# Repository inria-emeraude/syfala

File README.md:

# syfala v0.10.0

Automatic compilation of Faust and C++ audio DSP programs for AMD/Xilinx FPGA platforms.

## Documentation and tutorials

The Syfala documentation is now centralized [here](https://inria-emeraude.github.io/syfala/). It includes information, examples and tutorials for the following topics: 

- Installing AMD/Xilinx **dependencies**.
- Installing and setting up the **syfala toolchain**.
- Running a simple example on a Digilent Zybo Z7 board, **using Faust**.
- Using C++ to program a more optimized DSP kernel.
- Building the **Embedded Linux** for Syfala.

## Supported board models

- [x] Digilent **Zybo Z7-10** - Zynq-7000 ARM/FPGA SoC Development Board
- [x] Digilent **Zybo Z7-20** - Zynq-7000 ARM/FPGA SoC Development Board
- [x] Digilent **Genesys ZU-3EG** - Zynq UltraScale+ MPSoC Development Board

and more to come...

## The syfala team

Here is a list of person that have contributed to the Syfala project :

- Tanguy Risset
- Yann Orlarey 
- Romain Michon
- Stephane Letz
- Florent de Dinechin
- Anastasia Volkova
- Alain Darte
- Yohan Uguen
- Gero Müller
- Adeyemi Gbadamosi
- Ousmane Touat
- Luc Forget
- Antonin Dudermel
- Maxime Popoff
- Thomas Delmas
- Oussama Bouksim
- Pierre Cochard
- Joseph Bizien
- Agathe Herrou
- Jurek Weber
- Aloïs Rautureau
- Jessica Zaki-Sewa
- Jonas Hoepner
- Benjamin Quiédeville
- Daniel Habib

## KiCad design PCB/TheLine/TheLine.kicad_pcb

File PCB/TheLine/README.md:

# The LINE

This directory contains the KiCad source files for **The LINE**, a modular 8-channel loudspeaker PCB module, along with `autogenerate.py`, a parametric generation script that can adapt the board layout to different loudspeaker dimensions and spacings without any manual PCB editing.

## Background

The LINE is an open-source, modular loudspeaker array platform designed for spatial audio research and artistic deployment. Each PCB module integrates eight MAX98357A digital audio amplifiers (DAC + Class-D power stage in one chip) and eight PCB-mounted loudspeakers. Modules are daisy-chained via identical 2×20 connectors and driven by an FPGA system-on-module (ALINX AC7020C, Xilinx Zynq-7000). A single FPGA can control up to three independent arrays of 32 modules each, for a theoretical maximum of 768 channels.

The PCB design is intentionally built around a repeated, identical functional block (one per loudspeaker) which makes the layout amenable to parametric generation. By specifying the loudspeaker width, height, and inter-speaker gap, `autogenerate.py` regenerates the full board layout automatically, repositioning all components, routing, zones, and silkscreen elements accordingly.

This approach was used, for instance, to adapt the board to the Tang Band W2-2136S loudspeakers used at the EMPAC/CCRMA installation at Stanford University, without modifying any schematic or routing logic by hand.

The full system is described in:

> Maxime Popoff, Romain Michon, Pierre Cochard, and Tanguy Risset.  
> *Embedded, Modular, and Affordable High-Density Loudspeaker Arrays.*  
> NIME '26, London, UK.

---

## Repository Structure

```
.
├── TheLine.kicad_pcb         # Template PCB (8-channel, default loudspeaker)
├── TheLine.kicad_sch         # KiCad schematic
├── TheLine.kicad_pro         # KiCad project file
├── autogenerate.py           # Parametric PCB generation script
├── gerbers/                  # Pre-generated Gerber files for the default design
└── README.md
```

The `autogenerate.py` script reads `TheLine.kicad_pcb` as its template and writes a new `.kicad_pcb` file with the updated geometry. It does not modify the schematic or the netlist.

---

## Dependencies

The script uses the **KiCad Python scripting API** (`pcbnew`), which is bundled with KiCad 7 and later. It does not require any additional Python packages.

**Requirements:**
- KiCad 7.x or 8.x installed
- Python 3.8+ (the one bundled with KiCad, or a system install where `pcbnew` is importable)

**Tested on Linux only**

---

## Usage

### Basic usage: change loudspeaker dimensions

```bash
python autogenerate.py \
  --input TheLine.kicad_pcb \
  --output TheLine_custom.kicad_pcb \
  --speaker-width 30.0 \
  --speaker-spacing 2.5 \
  --speaker-height 95.0
```

This generates a new board where each loudspeaker slot is 30 mm wide, separated by 2.5 mm gaps, with a board height of 95 mm. All component placements, tracks, copper zones, and silkscreen elements are repositioned accordingly.

### Preview without writing (dry run)

```bash
python autogenerate.py \
  --input TheLine.kicad_pcb \
  --output TheLine_custom.kicad_pcb \
  --speaker-width 30.0 \
  --dry-run
```

The script prints a summary of the computed geometry without writing any file. Useful for checking dimensions before committing.

### Replace the loudspeaker footprint

If your loudspeakers have a different pad layout than the default ASB05708CO-LW100-R, you can supply a custom footprint from a separate `.kicad_pcb` file. The script will extract the first `LS*`-referenced footprint from that file and substitute it for every speaker position on the generated board.

```bash
python autogenerate.py \
  --input TheLine.kicad_pcb \
  --output TheLine_custom.kicad_pcb \
  --speaker-width 38.0 \
  --speaker-spacing 3.0 \
  --custom-footprint my_speaker_footprint.kicad_pcb
```

The custom footprint board should contain exactly one footprint with a reference matching `LS\d+` (e.g. `LS1`). Pad net assignments are inferred automatically by pad number from the original design.

---

## Command-line Reference

| Argument | Type | Default | Description |
|---|---|---|---|
| `--input` | path | `../TheLine.kicad_pcb` | Input template PCB file |
| `--output` | path | `TheLine_parametric.kicad_pcb` | Output PCB file |
| `--speaker-width` | float (mm) | `23.0` | Width of one loudspeaker/amplifier block |
| `--speaker-spacing` | float (mm) | `2.0` | Gap between two adjacent blocks |
| `--speaker-height` | float (mm) | `90.0` | Board height (minimum 90 mm) |
| `--custom-footprint` | path | *(none)* | Path to a `.kicad_pcb` file whose first `LS*` footprint replaces every speaker footprint |
| `--dry-run` | flag | `False` | Print geometry summary without writing output |

---

## How the Script Works

The script operates entirely through the `pcbnew` API and does not touch the KiCad file as raw text (except for the footprint substitution step, which uses S-expression parsing for UUID deduplication).

At a high level, it:

1. Loads the template board and locates all `LS*` speaker footprints.
2. Computes the desired X positions of each speaker based on the requested width and spacing, starting from the leftmost speaker's current position.
3. For each component, track, copper zone, and silkscreen element in the parametric channel band, it determines which loudspeaker "column" it belongs to and applies the corresponding X offset.
4. Long horizontal bus tracks (the shared I²S/TDM signal bus) are stretched or compressed at both ends independently to span the full new board width.
5. The fixed solder-jumper strip (JP1–JP32, used for module addressing) is moved as a rigid group to stay flush with the right edge.
6. Connectors J1/J2 (left side) and J3/J4 (right side) are repositioned to maintain their distance from the board edges.
7. Power plane zones are redrawn to fill the new board outline.
8. Copper zones are refilled.
9. Speaker outlines are redrawn on `Dwgs.User` and `F.Silkscreen`.

The script preserves clock buffering connections and all net assignments. It does not regenerate routing for the signal fanout; those sections are moved rigidly.

---

## PCB Manufacturing Notes

The design targets standard 2-layer PCB manufacturing (1.6 mm FR4). The default board is approximately 190 × 90 mm. Most prototype PCB services (JLCPCB, PCBWay, etc.) can manufacture this size at low cost.

The maximum board size supported by this parametric approach, given typical manufacturer panel limits, is around 600 × 700 mm (which would accommodate a minimum loudspeaker spacing of approximately 75 mm in the most constrained configuration).

Pre-generated Gerber files for the default 8-speaker, 24 mm pitch configuration are in the `gerbers/` directory.

---

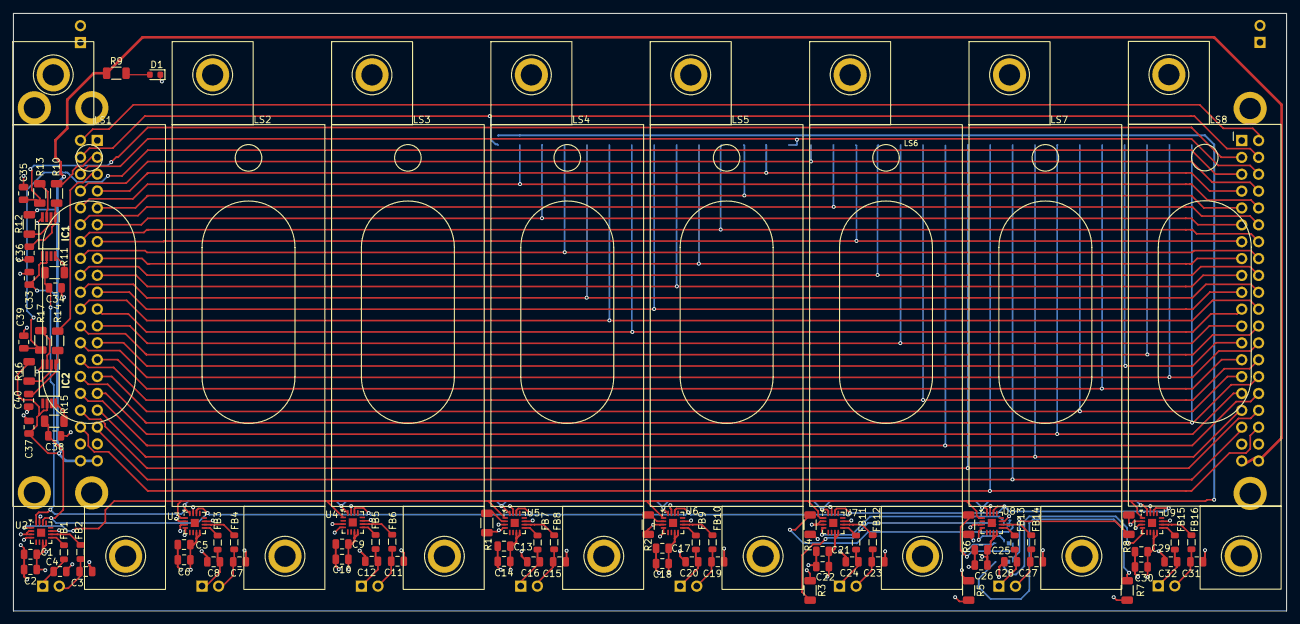
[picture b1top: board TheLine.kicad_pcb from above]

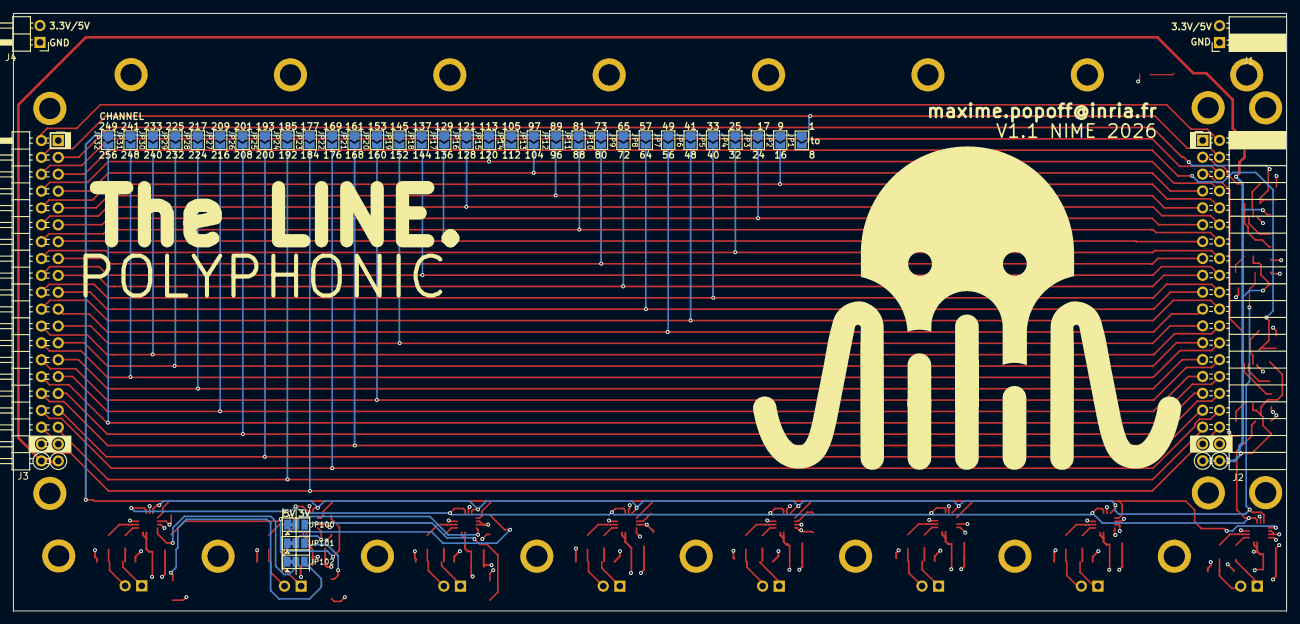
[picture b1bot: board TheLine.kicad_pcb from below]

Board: 4 copper layers, 191.8 x 90.0 mm, 131 parts (37 on the bottom side), 95 nets.

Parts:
C1, C5, C9, C13, C17, C21, C25, C29: 0.1uF; C_0805_2012Metric
C2, C6, C10, C14, C18, C22, C26, C30: 10uF; C_0805_2012Metric
C3, C4, C7, C8, C11, C12, C15, C16, C19, C20, C23, C24, C27, C28, C31, C32: 220p; C_0805_2012Metric
C33, C37: 100n; C_0805_2012Metric
C34, C35, C36, C38, C39, C40: DNP; C_0805_2012Metric
D1: LED; LED_0603_1608Metric
FB1, FB2, FB3, FB4, FB5, FB6, FB7, FB8, FB9, FB10, FB11, FB12, FB13, FB14, FB15, FB16: Ferrite; L_0805_2012Metric
IC1, IC2: LMK1C1102PWR; SOP65P640X120-8N
J1: Conn_01x02; PinSocket_1x02_P2.54mm_Horizontal
J2: Conn_02x20_Odd_Even; PinSocket_2x20_P2.54mm_Horizontal
J3: Conn_02x20_Odd_Even; PinHeader_2x20_P2.54mm_Horizontal
J4: Conn_01x02; PinHeader_1x02_P2.54mm_Horizontal
JP1, JP2, JP3, JP4, JP5, JP6, JP7, JP8, JP9, JP10, JP11, JP12, JP13, JP14, JP15, JP16, JP17, JP18, JP19, JP20, JP21, JP22, JP23, JP24, JP25, JP26, JP27, JP28, JP29, JP30, JP31, JP32: Jumper_2_Open; SolderJumper-2_P1.3mm_Open_TrianglePad1.0x1.5mm
JP100, JP101, JP102: jumper; SolderJumper-3_P1.3mm_Bridged12_Pad1.0x1.5mm
LS1, LS2, LS3, LS4, LS5, LS6, LS7, LS8: Speaker; ASB05708CO-LW100-R
R1, R2: 100k; R_1206_3216Metric
R3, R5, R7: 634k; R_1206_3216Metric
R4, R6, R8: 1M; R_1206_3216Metric
R9: 1k; R_1206_3216Metric
R10, R14: 22; R_1206_3216Metric
R11, R13, R15, R17: 0; R_1206_3216Metric
R12, R16: 10k; R_1206_3216Metric
U2, U3, U4, U5, U6, U7, U8, U9: MAX98357A; TQFN-16-1EP_3x3mm_P0.5mm_EP1.23x1.23mm

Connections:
/DAC1/OUT+: C4.1, FB1.2, LS1.1
/DAC1/OUT-: C3.1, FB2.2, LS1.2
/DAC2/OUT+: C8.1, FB3.2, LS2.1
/DAC2/OUT-: C7.1, FB4.2, LS2.2
/DAC3/OUT+: C12.1, FB5.2, LS3.1
/DAC3/OUT-: C11.1, FB6.2, LS3.2
/DAC4/GAIN: R1.1, U5.2 (GAIN_SLOT)
/DAC4/OUT+: C16.1, FB7.2, LS4.1
/DAC4/OUT-: C15.1, FB8.2, LS4.2
/DAC5/GAIN: R2.1, U6.2 (GAIN_SLOT)
/DAC5/OUT+: C20.1, FB9.2, LS5.1
/DAC5/OUT-: C19.1, FB10.2, LS5.2
/DAC6/MODE: JP100.2 (C), U7.4 (~SD_MODE)
/DAC6/OUT+: C24.1, FB11.2, LS6.1
/DAC6/OUT-: C23.1, FB12.2, LS6.2
/DAC7/MODE: JP101.2 (C), U8.4 (~SD_MODE)
/DAC7/OUT+: C28.1, FB13.2, LS7.1
/DAC7/OUT-: C27.1, FB14.2, LS7.2
/DAC8/MODE: JP102.2 (C), U9.4 (~SD_MODE)
/DAC8/OUT+: C32.1, FB15.2, LS8.1
/DAC8/OUT-: C31.1, FB16.2, LS8.2
/Pin_2: J2.2, J3.2
/Pin_3: J2.3, R10.1
/Pin_3_OUT: C35.2, J3.3, R13.1
/Pin_4: J2.4, J3.4, JP1.2 (B)
/Pin_5: J2.5, R14.1
/Pin_5_OUT: C39.2, J3.5, R17.1
/Pin_6: J2.6, J3.6, JP14.2 (B)
/Pin_7: J2.7, J3.7, JP13.2 (B)
/Pin_8: J2.8, J3.8, JP15.2 (B)
/Pin_9: J2.9, J3.9, JP12.2 (B)
/Pin_10: J2.10, J3.10, JP2.2 (B)
/Pin_11: J2.11, J3.11, JP3.2 (B)
/Pin_12: J2.12, J3.12, JP16.2 (B)
/Pin_13: J2.13, J3.13, JP17.2 (B)
/Pin_14: J2.14, J3.14, JP11.2 (B)
/Pin_15: J2.15, J3.15, JP10.2 (B)
/Pin_16: J2.16, J3.16, JP4.2 (B)
/Pin_17: J2.17, J3.17, JP9.2 (B)
/Pin_18: J2.18, J3.18, JP18.2 (B)
/Pin_19: J2.19, J3.19, JP8.2 (B)
/Pin_20: J2.20, J3.20, JP5.2 (B)
/Pin_21: J2.21, J3.21, JP7.2 (B)
/Pin_22: J2.22, J3.22, JP6.2 (B)
/Pin_23: J2.23, J3.23, JP19.2 (B)
/Pin_24: J2.24, J3.24, JP30.2 (B)
/Pin_25: J2.25, J3.25, JP29.2 (B)
/Pin_26: J2.26, J3.26, JP31.2 (B)
/Pin_27: J2.27, J3.27, JP28.2 (B)
/Pin_28: J2.28, J3.28, JP20.2 (B)
/Pin_29: J2.29, J3.29, JP27.2 (B)
/Pin_30: J2.30, J3.30, JP32.2 (B)
/Pin_31: J2.31, J3.31, JP26.2 (B)
/Pin_32: J2.32, J3.32, JP21.2 (B)
/Pin_33: J2.33, J3.33, JP25.2 (B)
/Pin_34: J2.34, J3.34, JP22.2 (B)
/Pin_35: J2.35, J3.35, JP24.2 (B)
/Pin_36: J2.36, J3.36, JP23.2 (B)
BCLK: C34.2, R11.2, U2.16 (BCLK), U3.16 (BCLK), U4.16 (BCLK), U5.16 (BCLK), U6.16 (BCLK), U7.16 (BCLK), U8.16 (BCLK), U9.16 (BCLK)
DIN: JP1.1 (A), JP2.1 (A), JP3.1 (A), JP4.1 (A), JP5.1 (A), JP6.1 (A), JP7.1 (A), JP8.1 (A), JP9.1 (A), JP10.1 (A), JP11.1 (A), JP12.1 (A), JP13.1 (A), JP14.1 (A), JP15.1 (A), JP16.1 (A), JP17.1 (A), JP18.1 (A), JP19.1 (A), JP20.1 (A), JP21.1 (A), JP22.1 (A), JP23.1 (A), JP24.1 (A), JP25.1 (A), JP26.1 (A), JP27.1 (A), JP28.1 (A), JP29.1 (A), JP30.1 (A), JP31.1 (A), JP32.1 (A), U2.1 (DIN), U3.1 (DIN), U4.1 (DIN), U5.1 (DIN), U6.1 (DIN), U7.1 (DIN), U8.1 (DIN), U9.1 (DIN)
GND: C1.2, C2.2, C3.2, C4.2, C5.2, C6.2, C7.2, C8.2, C9.2, C10.2, C11.2, C12.2, C13.2, C14.2, C15.2, C16.2, C17.2, C18.2, C19.2, C20.2, C21.2, C22.2, C23.2, C24.2, C25.2, C26.2, C27.2, C28.2, C29.2, C30.2, C31.2, C32.2, C33.2, C34.1, C35.1, C36.1, C37.2, C38.1, C39.1, C40.1, D1.1 (K), IC1.4 (GND), IC2.4 (GND), J1.1, J2.1, J2.37, J2.38, J3.1, J3.37, J3.38, J4.1, R2.2, U2.2 (GAIN_SLOT), U2.3 (GND), U2.11 (GND), U2.15 (GND), U3.3 (GND), U3.11 (GND), U3.15 (GND), U4.3 (GND), U4.11 (GND), U4.15 (GND), U5.3 (GND), U5.11 (GND), U5.15 (GND), U6.3 (GND), U6.11 (GND), U6.15 (GND), U7.2 (GAIN_SLOT), U7.3 (GND), U7.11 (GND), U7.15 (GND), U8.3 (GND), U8.11 (GND), U8.15 (GND), U9.3 (GND), U9.11 (GND), U9.15 (GND)
LRBCLK: C38.2, R15.2, U2.14 (LRCLK), U3.14 (LRCLK), U4.14 (LRCLK), U5.14 (LRCLK), U6.14 (LRCLK), U7.14 (LRCLK), U8.14 (LRCLK), U9.14 (LRCLK)
unnamed: D1.2 (A), R9.2
unnamed: IC1.2 (1G), R12.2
unnamed: C36.2, IC1.1 (CLKIN), R10.2
unnamed: IC1.3 (Y0), R13.2
unnamed: IC1.8 (Y1), R11.1
unnamed: IC2.2 (1G), R16.2
unnamed: C40.2, IC2.1 (CLKIN), R14.2
unnamed: IC2.3 (Y0), R17.2
unnamed: IC2.8 (Y1), R15.1
unnamed: JP100.1 (A), R4.1
unnamed: JP100.3 (B), R3.1
unnamed: JP101.1 (A), R6.1
unnamed: JP101.3 (B), R5.1
unnamed: JP102.1 (A), R8.1
unnamed: JP102.3 (B), R7.1
unnamed: FB2.1, U2.10 (OUTN)
unnamed: FB1.1, U2.9 (OUTP)
unnamed: FB4.1, U3.10 (OUTN)
unnamed: FB3.1, U3.9 (OUTP)
unnamed: FB6.1, U4.10 (OUTN)
unnamed: FB5.1, U4.9 (OUTP)
unnamed: FB8.1, U5.10 (OUTN)
unnamed: FB7.1, U5.9 (OUTP)
unnamed: FB10.1, U6.10 (OUTN)
unnamed: FB9.1, U6.9 (OUTP)
unnamed: FB12.1, U7.10 (OUTN)
unnamed: FB11.1, U7.9 (OUTP)
unnamed: FB14.1, U8.10 (OUTN)
unnamed: FB13.1, U8.9 (OUTP)
unnamed: FB16.1, U9.10 (OUTN)
unnamed: FB15.1, U9.9 (OUTP)
VCC: C33.1, C37.1, IC1.6 (VDD), IC2.6 (VDD), J2.39, J2.40, J3.39, J3.40, R9.1, R12.1, R16.1
VDD: C1.1, C2.1, C5.1, C6.1, C9.1, C10.1, C13.1, C14.1, C17.1, C18.1, C21.1, C22.1, C25.1, C26.1, C29.1, C30.1, J1.2, J4.2, R1.2, R3.2, R4.2, R5.2, R6.2, R7.2, R8.2, U2.4 (~SD_MODE), U2.7 (VDD), U2.8 (VDD), U3.2 (GAIN_SLOT), U3.4 (~SD_MODE), U3.7 (VDD), U3.8 (VDD), U4.4 (~SD_MODE), U4.7 (VDD), U4.8 (VDD), U5.4 (~SD_MODE), U5.7 (VDD), U5.8 (VDD), U6.4 (~SD_MODE), U6.7 (VDD), U6.8 (VDD), U7.7 (VDD), U7.8 (VDD), U8.7 (VDD), U8.8 (VDD), U9.2 (GAIN_SLOT), U9.7 (VDD), U9.8 (VDD)

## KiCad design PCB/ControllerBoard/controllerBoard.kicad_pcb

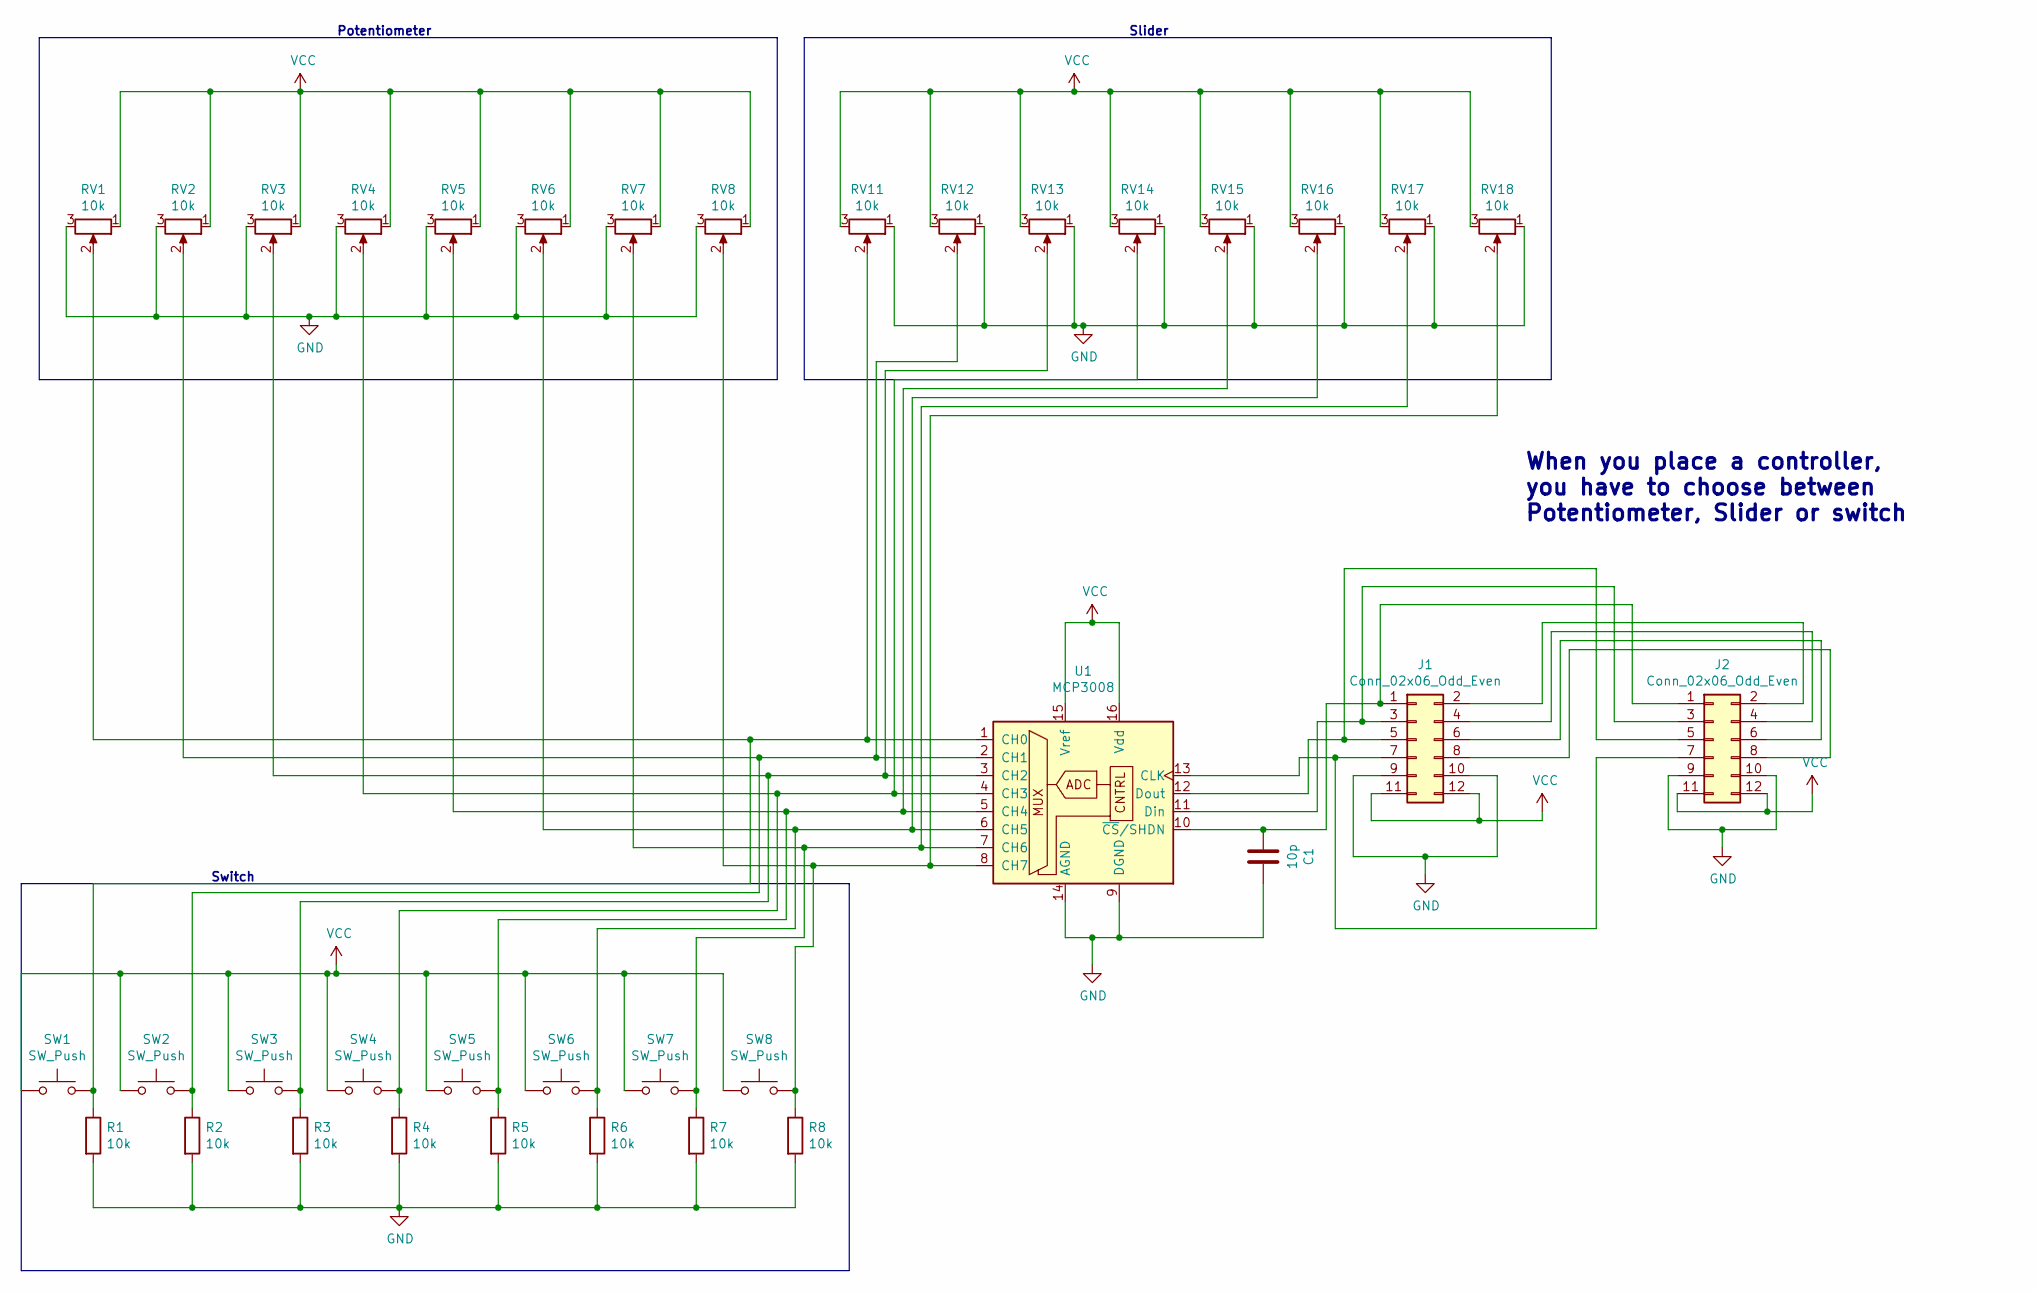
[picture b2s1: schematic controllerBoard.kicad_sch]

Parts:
C1: 10p; C_Disc_D5.0mm_W2.5mm_P2.50mm
J1: Conn_02x06_Odd_Even; PinHeader_2x06_P2.54mm_Horizontal
J2: Conn_02x06_Odd_Even; PinHeader_2x06_P2.54mm_Vertical
R1, R2, R3, R4, R5, R6, R7, R8: 10k; R_Axial_DIN0207_L6.3mm_D2.5mm_P7.62mm_Horizontal
RV1, RV2, RV3, RV4, RV5, RV6, RV7, RV8: 10k; Potentiometer_Omeg_PC16BU_Vertical
RV11, RV12, RV13, RV14, RV15, RV16, RV17, RV18: 10k; Potentiometer_Bourns_PTA6043_Single_Slide
SW1, SW2, SW3, SW4, SW5, SW6, SW7, SW8: SW_Push; SW_PUSH_6mm
U1: MCP3008; DIP-16_W7.62mm_Socket_LongPads

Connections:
GND: C1.1, J1.9, J1.10, J2.9, J2.10, R1.2, R2.2, R3.2, R4.2, R5.2, R6.2, R7.2, R8.2, RV1.3, RV2.3, RV3.3, RV4.3, RV5.3, RV6.3, RV7.3, RV8.3, RV11.1, RV12.1, RV13.1, RV14.1, RV15.1, RV16.1, RV17.1, RV18.1, U1.9 (DGND), U1.14 (AGND)
unnamed: C1.2, J1.1, J2.1, U1.10 (~CS/SHDN)
unnamed: J1.2, J2.2
unnamed: J1.3, J2.3, U1.11 (Din)
unnamed: J1.4, J2.4
unnamed: J1.5, J2.5, U1.12 (Dout)
unnamed: J1.6, J2.6
unnamed: J1.7, J2.7, U1.13 (CLK)
unnamed: J1.8, J2.8
unnamed: R1.1, RV1.2, RV11.2, SW1.2, U1.1 (CH0)
unnamed: R2.1, RV2.2, RV12.2, SW2.2, U1.2 (CH1)
unnamed: R3.1, RV3.2, RV13.2, SW3.2, U1.3 (CH2)
unnamed: R4.1, RV4.2, RV14.2, SW4.2, U1.4 (CH3)
unnamed: R5.1, RV5.2, RV15.2, SW5.2, U1.5 (CH4)
unnamed: R6.1, RV6.2, RV16.2, SW6.2, U1.6 (CH5)
unnamed: R7.1, RV7.2, RV17.2, SW7.2, U1.7 (CH6)
unnamed: R8.1, RV8.2, RV18.2, SW8.2, U1.8 (CH7)
VCC: J1.11, J1.12, J2.11, J2.12, RV1.1, RV2.1, RV3.1, RV4.1, RV5.1, RV6.1, RV7.1, RV8.1, RV11.3, RV12.3, RV13.3, RV14.3, RV15.3, RV16.3, RV17.3, RV18.3, SW1.1, SW2.1, SW3.1, SW4.1, SW5.1, SW6.1, SW7.1, SW8.1, U1.15 (Vref), U1.16 (Vdd)

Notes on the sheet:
Switch
When you place a controller, you have to choose between Potentiometer, Slider or switch
Potentiometer
Slider

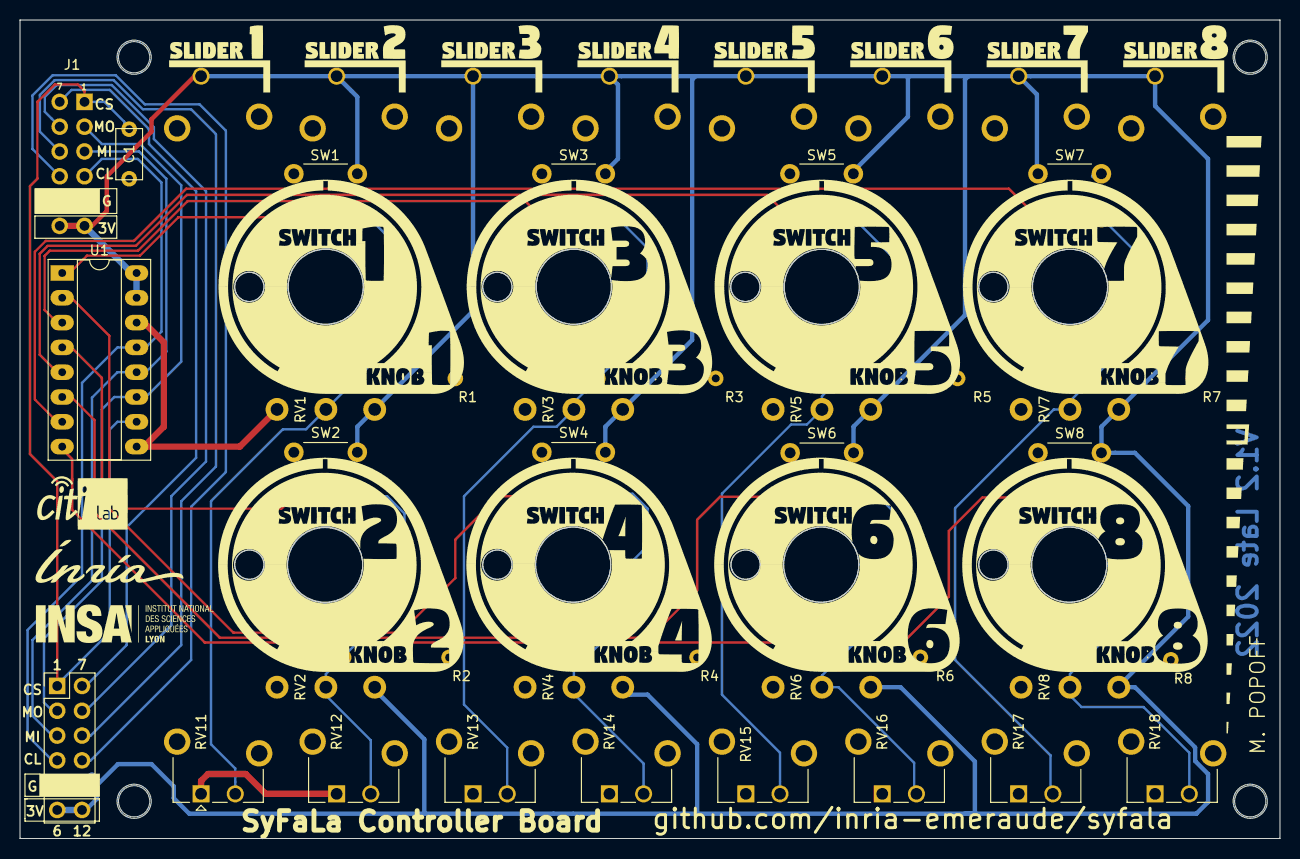
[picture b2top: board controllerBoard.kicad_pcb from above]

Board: 2 copper layers, 129.0 x 83.8 mm, 37 parts (0 on the bottom side), 18 nets.

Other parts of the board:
svg2mod: G***; templateHCB

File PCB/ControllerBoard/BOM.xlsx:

|  |  | xxxx xxxx xxxxx xxPCS BOM (Sample Bill of Materials)
Item # | *Designator | *Qty | Manufacturer | *Mfg Part # | Description / Value | *Package/Footprint | Type | Your Instructions / Notes
1 | C1 | 1 | Any / Open | Any / Open | Capacitor_THT 10pf | D5.0mm_W2.5mm_P2.50mm | thru-hole
2 | J1 | 1 | Any / Open | Any / Open | Connector_PinHeader_2.54mm:PinHeader_2x06_P2.54mm_Horizontal | 2x06_P2.54mm | thru-hole
3 | J2 | 1 | Any / Open | Any / Open | Connector_PinHeader_2.54mm:PinHeader_2x06_P2.54mm_Vertical | 2x06_P2.54mm | thru-hole
4 | R1, R2, R3, R4, R5, R6, R7, R8 * | 8 | Any / Open | Any / Open | Resistor_THT 10k R_Axial_DIN0207_Horizontal | L6.3mm_D2.5mm_P7.62mm | thru-hole
5 | RV1, RV2, RV3, RV4, RV5, RV6, RV7, RV8 * | 8 | TT ELECTRONICS / BI TECHNOLOGIES | P160KN-0QD15B10K * | Potentiometer 10k linear shaft diameter=6mm * | 10mm | thru-hole
6 | RV11, RV12, RV13, RV14, RV15, RV16, RV17, RV18 * | 8 | BOURNS | PTA6043-2015DPB10 | Potentiometer slider 10k | PTA6043_Single_Slide | thru-hole
7 | SW1, SW2, SW3, SW4, SW5, SW6, SW7, SW8 * | 8 | Any / Open | Any / Open | SWITCH TACTILE SPST-NO 6mm | 6.5mm * 4.5mm | thru-hole
8 | U1 | 1 | Microchip | MCP3008-I/P | Package_DIP:DIP-16_W7.62mm_Socket_LongPads | DIP-16_W7.62mm | thru-hole
9 | OPTIONAL |  |  | MC170841CR MC170842CR MC170843CR MC170844CR MC170845CR MC170846CR MC170852CR | Potentiometer knob
 |  |  |  |  | *This reference is a straight pin potentiometer. So you will have to bend the p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
 | * You don’t need 8 of each. Please for each controller (1 to 8), choose between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

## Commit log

2022-02-18 added syfala-project files
2022-02-18 created master-zybo
2022-02-18 added syfala-getting-started.pdf
2022-02-18 set the new i2S_transceiver.vhd
2022-02-18 rewrite README
2022-02-18 moved standalone_boot to boot
2022-02-18 modify main branch README.md
2022-02-21 added testbench for new i2s code (Fev. 2022)
2022-02-21 modified main branch README.md
2022-02-21 merged main branch for README
2022-02-23 Improve README.
2022-02-23 corrected main branch makefile
2022-02-23 modified syfala-getting-started.pdf
2022-02-28 suppressed testbench from master zybo
2022-02-28 restore README.md
2022-03-03 Rebuild from scratch to clean project; Add bargraph; New UART handler
2022-03-14 New Zybo onboard interface (LED/Button)
2022-03-15 added testbench_new_i2s
2022-03-16 Adjust README to new interface, support Z20 version
2022-03-16 Readme fix
2022-03-16 adjust configFAUST.H to default config
2022-07-11 added smoo in echo.dsp
2022-08-29 [general] v7 as main
2022-08-30 [general] changing back SYSCL_I2S_RATIO to 10 for Zybo models
2022-08-31 [general] main update
2022-09-20 [general] mirror update
2022-09-22 [general] re-added bd_res .config files
2022-09-22 added Makefile in getting-started
2022-09-23 [general] clock update & misc
2022-10-13 [general] 1.1 zybo board parts
2022-11-15 [PCB] fix image
2023-02-17 [control] added MIDI->UART control
2023-03-01 v0.7.1
2023-04-17 [linux] dev/linux branch
2023-09-25 Adding documentation webiste basic frame
2023-09-25 Moving website to docs folder
2023-09-25 Populating website
2023-09-25 Adding missing Makefile
2023-10-13 [general] default Xilinx toolchain version is now 2022.2
2023-10-13 [README] updated contributors
2023-11-20 [paw] gitlab update
2023-11-24 [tools] patch report for linux
2023-12-02 adding ethernet extension
2023-12-04 adding ethernet extension (#2)
2023-12-04 [eth] removing compiler warning
2023-12-07 [cpp] added 'modes' example
2024-01-09 [github] dev/main
2024-01-09 [github] update .gitignore and missing files
2024-02-13 [github] gitlab update
2024-02-13 dev/main (#3)
    * [github] dev/main
    * [github] update .gitignore and missing files
    * [github] gitlab update
2024-03-12 Deployed c893f4c with MkDocs version: 1.4.2
2024-03-12 [mkdocs] update
2024-03-12 [mkdocs] reload
2024-03-12 [mkdocs] added tutorials, fixed a few theme-related issues
2024-03-12 [mkdocs] changed theme, few corrections
2024-03-12 [mkdocs] docs/ update
2024-03-12 [doc] updated README and webdoc index
2024-03-12 [mkdocs] updated cpp tutorial, few overall corrections
2024-03-12 [doc] cleanup
2024-03-13 [PCB] Add Frugal and ULL boards
2024-03-15 [doc] few corrections
2024-04-01 Add Vocoder cpp Examples
2024-04-02 Vocoder IMT Atlantique ProCom Project (#4)
    * Add Vocoder cpp Examples
    * Add Vocoder cpp Examples
    * Add Vocoder cpp Examples
2024-10-18 [github] dev update
2024-10-23 [github] main update
2024-10-23 Deployed d3233e5 with MkDocs version: 1.5.3
2024-10-23 [pages] commit docs
2024-10-25 [doc] flatpak update
2024-11-22 [vhdl] vhdl target (experimental) support
2024-11-22 [vhdl] remove maxthreads parameters
2024-11-22 [vhdl] add faust2vhdl packages
2024-11-22 [vhdl] fix arm app
2025-07-30 Add Quick Test to Getting started
2025-07-30 [doc] update
2025-10-09 [alpine] fetch llvm20 from edge/main for newer faust-dev package
2026-03-03 re-push PCB designs
2026-03-06 updated linux tutorial doc
2026-03-06 update linux tutorial
2026-03-10 corrected a small bug of syfala report
2026-03-11 added sine.txt in stimuli
2026-04-28 Add TheLine PCB
2026-06-03 add The Line readme
2026-06-03 Add README PCBs
2026-06-03 add image ULL
